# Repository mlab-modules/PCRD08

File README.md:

# PCRD08 - Analogue backend for SiPM detectors with scintillation crystals

Analogue front-end and ADC module for radiation detectors based on silicon photomultipliers (SiPM) coupled to scintillation crystals. The module amplifies the SiPM pulses, detects a threshold crossing, and digitizes the signal for a controlling MCU over SPI.

### Principle of function

The detector signal enters through the MCX connector J201 and is AC-coupled into a non-inverting amplifier (U201, AD8691). A second AD8691 stage (U204) provides additional gain before the signal reaches the LTC1865-MS ADC (U207), which is read out over SPI. A comparator (U203, TS3021ILT) together with a D flip-flop (U205, SN74LVC2G74) latches a digital flag whenever the signal crosses a threshold, which the controlling MCU can use to time the ADC conversion (CONV/RST/SCK/SDI/SDO are supplied by the host over the module's socket interface).

### Difference from PCRD07

PCRD08 reuses the general architecture of the older [PCRD07](https://github.com/mlab-modules/PCRD07) analogue backend (dual AD8691 gain stages, TS3021ILT comparator, LTC1865-MS ADC), but the analogue signal processing was reworked for SiPM+scintillator pulses, which are positive-going:

- **Input polarity** - PCRD07 (both revision A and B) amplifies the input signal with an inverting first stage (signal fed into the op-amp's `-` input, gain set by the feedback/input resistor ratio). PCRD08's input stage (U201) instead feeds the signal into the op-amp's `+` input, giving a non-inverting, unity-gain-at-high-frequency response suited to positive pulses.
- **No analogue sample-and-hold switch** - PCRD07 uses an analogue switch (TS5A4594) driven by its comparator/flip-flop pair to freeze the peak voltage on a storage capacitor, i.e. a true analogue peak-detector/memory circuit. PCRD08 has no such switch or hold capacitor; its comparator/flip-flop pair (U203/U205) only produces a digital threshold-crossing flag, and the ADC conversion is triggered directly by the host rather than sampling a held analogue voltage.

(Verified by comparing `hw/sch_pcb/analogue_backend.kicad_sch` of both modules.)

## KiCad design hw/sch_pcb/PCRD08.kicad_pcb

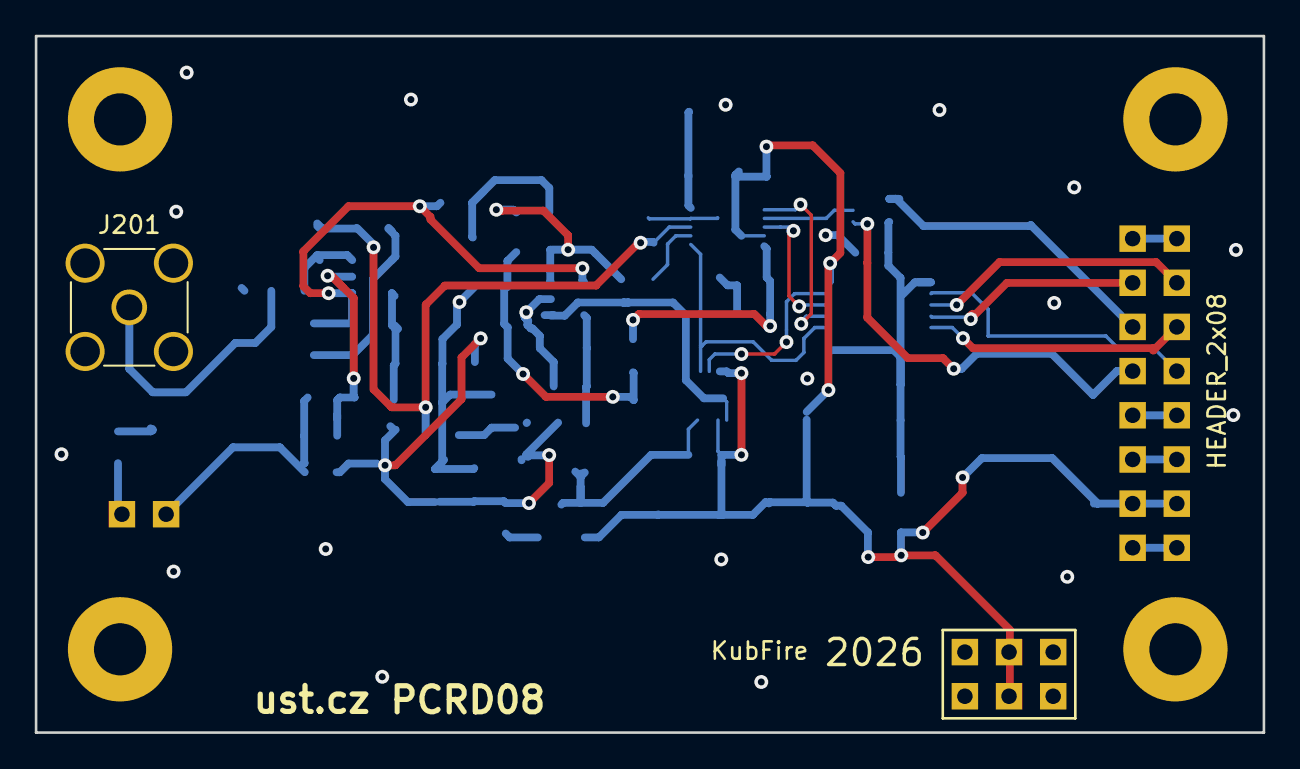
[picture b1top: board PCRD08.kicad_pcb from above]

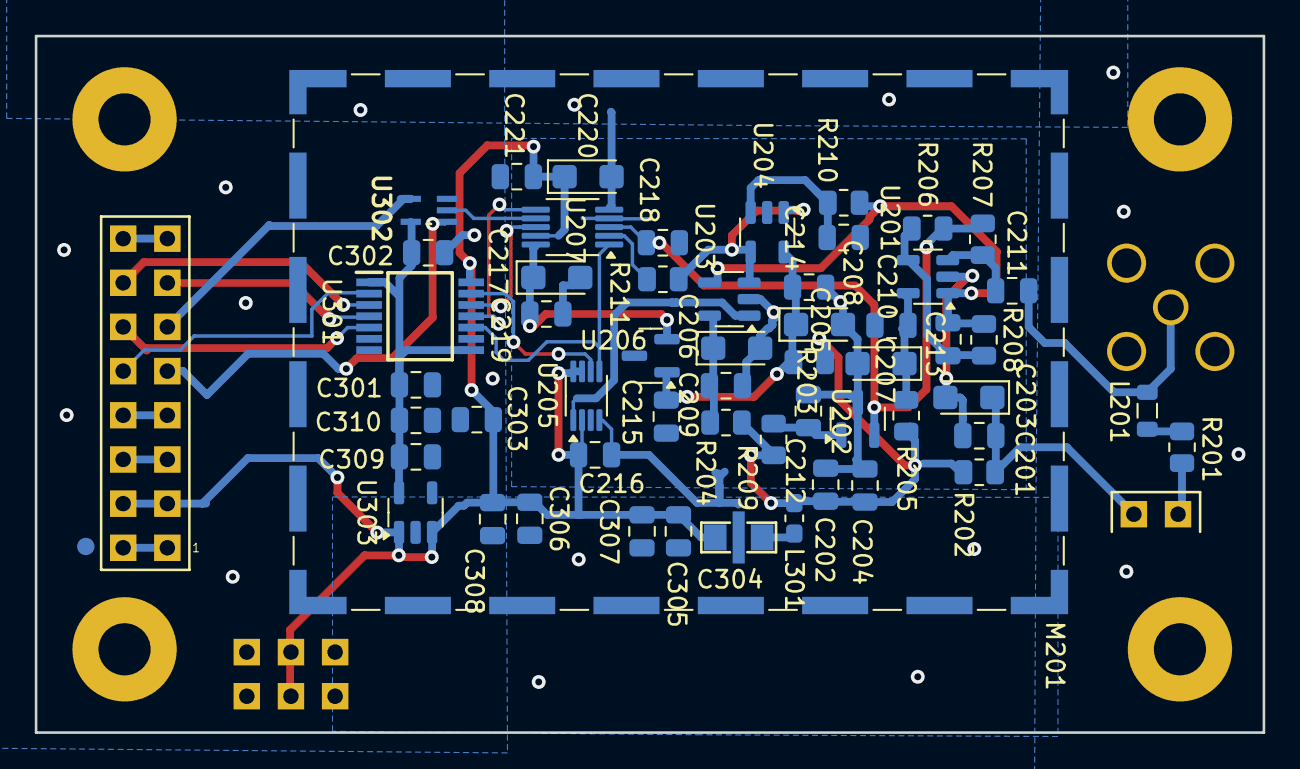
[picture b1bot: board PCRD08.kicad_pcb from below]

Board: 2 copper layers, 70.6 x 40.1 mm, 62 parts (59 on the bottom side), 36 nets.

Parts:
C201, C202, C204, C208, C209, C210, C212, C215, C216, C219, C221, C301, C302, C303, C305, C308, C310: 100nF; C_0805_2012Metric
C203, C205, C206, C207, C217, C220: 10uF; CP_EIA-3216-18_Kemet-A
C211, C213, C214, C218: 1nF; C_0805_2012Metric
C304: 1uF; FIR_0805
C306, C307, C309: 10uF; C_0805_2012Metric
FID104: Fiducial; Fiducial_1mm_Mask2mm
J201: MCX; SMA_Amphenol_901-144_Vertical
J202: HEADER_2x01; Straight_2x01
J301: HEADER_2x03; Straight_2x03
J302: HEADER_2x08; Straight_2x08
JP201: Jumper_2_Bridged; NetTie-2_SMD_Pad0.5mm
L201: L; L_0805_2012Metric
L301: NL03KT330; L_0603_1608Metric_Pad1.05x0.95mm_HandSolder
M103: HOLE; MountingHole_3mm
M201: RFShield_TwoPieces; Laird_Technologies_BMI-S-210-F_44.00x30.50mm
R201, R203, R204, R205, R206: 100; R_0805_2012Metric
R202, R211: 10; R_0805_2012Metric
R207, R208: 1k; R_0805_2012Metric
R209: 470R; R_0805_2012Metric
R210: 10k; R_0805_2012Metric
U201, U204: AD8691; TSOT-23-5
U202: ISL21080DIH309; SOT-23
U203: TS3021ILT; SOT-23-5
U205: SN74LVC2G74; VSSOP-8_2.3x2mm_P0.5mm
U206: ISL21080CIH341Z-TK; SOT-23
U207: LTC1865-MS; MSOP-10_3x3mm_P0.5mm
U301: TXU0304PWR; SOP65P640X120-14N
U302: SN74LVC1G125DCKT; SOT65P210X110-5N
U303: MIC5504-3.3YM5-TR; SOT-23-5

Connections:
+3.3V: C301.1, C302.1, C309.1, C310.1, U301.1 (VCCA), U301.8 (OE), U302.5 (VCC), U303.5 (VOUT)
+5V: C202.1, C204.1, L301.1, R202.2, R203.2, R204.2, R205.2, R209.2
+5VD: C216.1, C220.1, C221.1, C303.1, C304.3, C305.1, C306.1, C307.1, C308.1, J301.3, J301.4, J302.3, J302.4, U205.2 (D), U205.7 (~PRE), U205.8 (VCC), U207.9 (V_{CC}), U301.14 (VCCB), U303.1 (VIN), U303.3 (EN)
/analogue_backend_1/4.1 V: C217.1, C219.1, U206.2 (Vout), U207.10 (V_{REF})
/analogue_backend_1/A/D: R211.1, U207.2 (CH0)
/analogue_backend_1/CONV: U205.5 (Q), U207.1 (CONV), U301.10 (B4)
/analogue_backend_1/REF: C218.1, R206.1, R207.1, U202.2 (Vout), U207.3 (CH1)
/analogue_backend_1/RST: U205.6 (~CLR), U301.13 (B1Y)
/analogue_backend_1/SCK: U207.8 (SCK), U301.12 (B2Y)
/analogue_backend_1/SDI: U207.6 (SDI), U301.11 (B3Y)
/analogue_backend_1/SDO: U207.7 (SDO), U302.2 (A)
/analogue_backend_1/VCC2: C205.1, C208.1, C215.1, R203.1, U204.5 (V+), U206.1 (Vin)
/analogue_backend_1/VCC3: C206.1, C209.1, R204.1, U203.5 (V+)
/analogue_backend_1/VCC5: C207.1, C210.1, R205.1, U201.5 (V+)
/interface/3v3: J302.5, J302.6
/interface/SOCKET_CONV: J302.12, U301.5 (A4Y)
/interface/SOCKET_MISO: J302.11, U302.4 (Y)
/interface/SOCKET_MOSI: J302.13, U301.4 (A3)
/interface/SOCKET_OE: J302.9, U302.1 (~OE)
/interface/SOCKET_RST: J302.10, U301.2 (A1)
/interface/SOCKET_SCLK: J302.14, U301.3 (A2)
GND: C216.2, C220.2, C221.2, C301.2, C302.2, C303.2, C304.2, C305.2, C306.2, C307.2, C308.2, C309.2, C310.2, J201.2 (Ext), J301.1, J301.2, J301.5, J301.6, J302.1, J302.2, J302.15, J302.16, JP201.2, M103.1, M201.1 (Shield), U205.4 (GND), U207.5 (DGND), U301.7 (GND), U302.3 (GND), U303.2 (GND)
GNDA: C201.2, C202.2, C203.2, C204.2, C205.2, C206.2, C207.2, C208.2, C209.2, C210.2, C212.2, C214.2, C215.2, C217.2, C218.2, C219.2, JP201.1, U201.2 (V-), U202.3 (GND), U203.2 (V-), U204.2 (V-), U206.3 (GND), U207.4 (AGND)
unnamed: C201.1, C203.1, J202.2, R202.1
unnamed: C304.1, L301.2
unnamed: C211.1, J201.1 (In), L201.2
unnamed: J202.1, R201.2
unnamed: J302.7, J302.8
unnamed: L201.1, R201.1
unnamed: C211.2, R207.2, U201.3 (+)
unnamed: C213.2, R206.2, R208.2, U201.4 (-)
unnamed: C212.1, R209.1, U202.1 (Vin)
unnamed: R211.2, U203.3 (+), U204.1, U204.4 (-)
unnamed: C213.1, R208.1, R210.2, U201.1, U203.4 (-)
unnamed: C214.1, R210.1, U204.3 (+)
unnamed: U203.1, U205.1 (C)

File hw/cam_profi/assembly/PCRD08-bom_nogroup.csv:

Component,Description,Part,References,Value,Footprint,Quantity Per PCB,Datasheet,ust_id,ust_id2,mf,description_1,package,mpn,price,oc_farnell,snapeda_link,mp,supplier,oc_newark,availability,check_prices,manufacturer_name,mouser_price-stock,mouser_part_number,height,arrow_price-stock,arrow_part_number,manufacturer_part_number
1,Unpolarized capacitor,C,C211C213C214C218,1nF,C_0805_2012Metric,4,,6508260b462c6d9e720541f1 651abc26462c6d9e720551fa 5c70984812875079b91f8ba6,,,,,,,,,,,,,,,,,,,,
2,Unpolarized capacitor,C,C201C202C204C208C209C210C212C215C216C219C221C301C302C303C305C308C310,100nF,C_0805_2012Metric,17,,6508260b462c6d9e720541f1 5c70984712875079b91f8b4c,,,,,,,,,,,,,,,,,,,,
3,"EMI filter, single capacitor",Filter_EMI_C,C304,1uF,FIR_0805,1,http://www.murata.com/~/media/webrenewal/support/library/cat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,5c70984412875079b91f880f,,,,,,,,,,,,,,,,,,,,
4,Polarized capacitor,C_Polarized,C203C205C206C207C217C220,10uF,CP_EIA-3216-18_Kemet-A,6,,65089dd0462c6d9e720542b3,,,,,,,,,,,,,,,,,,,,
5,Unpolarized capacitor,C,C306C307C309,10uF,C_0805_2012Metric,3,,5c70984712875079b91f8b53,,,,,,,,,,,,,,,,,,,,
6,2x01 2.54 mm pitch header,HEADER_2x01,J202,HEADER_2x01,Straight_2x01,1,,,,,,,,,,,,,,,,,,,,,,
7,2x03 2.54 mm pitch header,HEADER_2x03,J301,HEADER_2x03,Straight_2x03,1,,,,,,,,,,,,,,,,,,,,,,
8,2x08 2.54 mm pitch header,HEADER_2x08,J302,HEADER_2x08,Straight_2x08,1,,,,,,,,,,,,,,,,,,,,,,
9,"coaxial connector (BNC, SMA, SMB, SMC, Cinch/RCA, LEMO, ...)",Conn_Coaxial,J201,MCX,SMA_Amphenol_901-144_Vertical,1,~,5fa10cc512875025b39779f6,,,,,,,,,,,,,,,,,,,,
10,Inductor,L,L201,L,L_0805_2012Metric,1,,626fd6fcdc56076e9a222966,,,,,,,,,,,,,,,,,,,,
11,"Inductor with ferrite core, small symbol",L_Ferrite_Small,L301,NL03KT330,L_0603_1608Metric_Pad1.05x0.95mm_HandSolder,1,,64fe1808f3b9d36f37fc944d,,,,,,,,,,,,,,,,,,,,
12,Two-piece EMI RF shielding cabinet,RFShield_TwoPieces,M201,RFShield_TwoPieces,Laird_Technologies_BMI-S-210-F_44.00x30.50mm,1,,5c70984312875079b91f873d,5c70984312875079b91f873c,,,,,,,,,,,,,,,,,,,
13,Resistor,R,R202R211,10,R_0805_2012Metric,2,,5c70984512875079b91f896d,,,,,,,,,,,,,,,,,,,,
14,Resistor,R,R201R203R204R205R206,100,R_0805_2012Metric,5,,5c70984512875079b91f8977 5c70984512875079b91f898c,,,,,,,,,,,,,,,,,,,,
15,Resistor,R,R209,470R,R_0805_2012Metric,1,,5c70984512875079b91f8986,,,,,,,,,,,,,,,,,,,,
16,Resistor,R,R207R208,1k,R_0805_2012Metric,2,,5c70984512875079b91f898c 5c70984612875079b91f899f,,,,,,,,,,,,,,,,,,,,
17,Resistor,R,R210,10k,R_0805_2012Metric,1,,5c70984612875079b91f899f,,,,,,,,,,,,,,,,,,,,
18,"Single Rail-to-Rail High Output Current Operational Amplifiers, SOT-23-5",AD8691,U201U204,AD8691,TSOT-23-5,2,https://www.analog.com/media/en/technical-documentation/data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,5d47c084128750448e6b4671,,,,,,,,,,,,,,,,,,,,
19,"2.0V 25μA Micropower Voltage Reference, SOT-23",ISL21070CIH320Z-TK,U206,ISL21080CIH341Z-TK,SOT-23,1,https://cz.mouser.com/datasheet/2/698/REN_isl21080_DST_20040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,6555591d0c8d609e3e79abc1,,,,,,,,,,,,,,,,,,,,
20,"2.0V 25μA Micropower Voltage Reference, SOT-23",ISL21070CIH320Z-TK,U202,ISL21080DIH309,SOT-23,1,https://www.renesas.com/us/en/document/dst/isl21080-datasheet,5c70984712875079b91f8b0b,,,,,,,,,,,,,,,,,,,,
21,"Dual channel 16-bit SAR Analog to Digital Converter, 5V supply, 150ksps, SPI interface",LTC1865-MS,U207,LTC1865-MS,MSOP-10_3x3mm_P0.5mm,1,https://www.analog.com/media/en/technical-documentation/data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,67f14385ee7fc534862c535e,,,,,,,,,,,,,,,,,,,,
22,"300mA Low-dropout Voltage Regulator, Vout 3.3V, Vin up to 5.5V, SOT-23",MIC5504-3.3YM5,U303,MIC5504-3.3YM5-TR,SOT-23-5,1,http://ww1.microchip.com/downloads/en/DeviceDoc/MIC550X.pdf,5c7255e81287500b4e112ea2,,,,,,,,,,,,,,,,,,,,
23,,SN74LVC1G125DCKT,U302,SN74LVC1G125DCKT,SOT65P210X110-5N,1,,,,Texas Instruments,"Buffer, Non-Inverting 1 Element 1 Bit per Element 3-State Output SC-70-5",SC70-5,SN74LVC1G125DCKT,None,1470733,https://www.snapeda.com/parts/SN74LVC1G125DCK/Texas+Instrume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,SN74LVC1G125DCK,Texas Instruments,22H0380,In Stock,https://www.snapeda.com/parts/SN74LVC1G125DCK/Texas+Instrume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,,,,,,,
24,"74AUC1G74, Single D Flip-Flop, Low-Voltage CMOS",74LVC2G74,U205,SN74LVC2G74,VSSOP-8_2.3x2mm_P0.5mm,1,https://www.ti.com/lit/ds/symlink/sn74lvc2g74-ep.pdf,65555d4795a79cc5ac409b41,,,,,,,,,,,,,,,,,,,,
25,"Single Rail-to-Rail High Output Current Operational Amplifiers, SOT-23-5",AD8691,U203,TS3021ILT,SOT-23-5,1,https://www.st.com/resource/en/datasheet/ts3021.pdf,5d47bfd4128750448e6b465e,,,,,,,,,,,,,,,,,,,,
26,Translation - Voltage Levels Four channel unidirectional level shifter,TXU0304PWR,U301,TXU0304PWR,SOP65P640X120-14N,1,,,,Texas Instruments,Four-channel fixed multidirectional level shifter,None,,None,,https://www.snapeda.com/parts/TXU0304PWR/Texas+Instruments/v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,TXU0304PWR,,,In Stock,https://www.snapeda.com/parts/TXU0304PWR/Texas+Instruments/v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,Texas Instruments,https://www.mouser.co.uk/ProductDetail/Texas-Instruments/TXU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,595-TXU0304PWR,1.2mm,https://www.arrow.com/en/products/txu0304pwr/texas-instrumen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,TXU0304PWR,TXU0304PWR
